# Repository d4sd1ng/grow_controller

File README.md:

# Growroom Control System

**Firmware (aktuelle Struktur):** [Sensor, Remote und C3](firmware/README.md). Die früheren Sketch-Ordner wurden entfernt; kein altes Installationsskript verwenden.

Streamlit dashboard for simulated sensors, VPD helpers, optional Telegram alerts, and GPIO simulation (runs anywhere with Python 3.11+).

**Aktuelle Sensor-Pinbelegung:** [Sensor/PINOUT.md](firmware/Sensor/PINOUT.md) · **Firmware:** [Sensor, Remote und C3](firmware/README.md) · **Deployment:** [deployment_vps.md](deployment_vps.md). Frühere Verdrahtungstexte sind nicht mehr gültig.

## Setup

```bash
python -m venv .venv
.venv\Scripts\activate   # Windows
pip install -r requirements.txt
```

Copy `.env.example` to `.env`. **Alle sensiblen und serverseitigen Settings** (Telegram, **`TELEMETRY_API_KEY`**, Ports, DB-Pfad, **`IOT_*`** für WLAN/Server-Host) kommen **nur aus `.env`** — der Python-Code nutzt `env_config`-Getter. Firmware: **`python export_firmware_secrets_from_env.py`** erzeugt git-ignorierte **`device_secrets.h`** pro Sketch aus derselben `.env`. **Telegram-Versand ist im Code aktuell auskommentiert** — Alerts landen in `alerts_log` und auf dem **CYD** (`/api/v1/mobile/summary`). Zum Reaktivieren in `main.py` die `telegram_notify`-Zeilen wieder einsetzen.

## Run

```bash
streamlit run main.py
```

**Telemetry-API** (ESP32 im Growroom → Server; **Cheap Yellow Display** holt die letzten Werte):

```bash
python run_telemetry_api.py
```

Standard: `http://<PC-IP>:8765` — u. a. `GET /api/v1/health` (SQLite-Ping, **ohne** API-Key), `POST /api/v1/telemetry`, `GET /api/v1/telemetry/series` (**echte Historie** aus SQLite, Parameter `hours` / `minutes` / `max_points`), `GET /api/v1/mobile/summary` (CYD: Messwerte + Relais + **Alerts**), `GET/POST /api/v1/control/*`. Optional **`X-Telemetry-Key`**. **`firmware/`**: Die aktuelle LVGL-Remote verwendet `/api/v1/mobile/summary` für Messwerte und `/api/v1/actuator/state` für den C3-Status.

Optional Telegram command bot (separate process; uses the same `.env` token):

```bash
python telegram_bot.py
```

## Telemetry (Speicher)

- Das Streamlit-Dashboard schreibt in **SQLite** nur, wenn sich Messwerte/Relais **merklich** ändern **oder** ein **Heartbeat** von ca. 60 s vergangen ist (weniger Reroll-Spam). ESP-/API-Ingest bleibt unverändert: jeder `POST /api/v1/telemetry` wie bisher eine Zeile.
- Speicherort: **`data/grow_telemetry.db`** standardmäßig (Ordner wird angelegt).
- Feste Spalten: Temperaturen, Luftfeuchte, Licht, EC, pH, vier Relais-Flags — passend zur Anzeige/Charts.
- Zusatzfelder aus dem ESP (andere Keys, verschachtelte Objekte) liegen als JSON in **`extras_json`** und gehen beim späteren Hardware-Import nicht verloren.
- **Retention:** alte Zeilen werden nach **`GROW_DATA_RETENTION_DAYS`** (Standard 90) gelöscht. **`GROW_DATA_DB=:memory:`** nur für Tests/ephemer.

Ursprünglich gedacht als zwei ESP32 (Sensoren + Relais) — **ein** Board reicht: Sensoren lesen, Relais schalten, ein Kanal (HTTP/MQTT/Serial) liefert JSON; der PC übernimmt Aggregation, Alerts und SQLite. Beim Anbinden echtes Payload-Felder auf die Tabellenspalten mappen (Relais ggf. aus `relays.heater` → Spalte `heater`).

## Security

**Eingrenzung:** Das Setup ist für ein **vertrauenswürdiges Heim-LAN** gedacht — nicht als hart abgesicherte Internet-API.

| Bereich | Stand im Projekt |
|--------|------------------|
| **Geheimnisse** | Tokens, API-Key, WLAN-Passwort nur in **`.env`** bzw. generiertem **`device_secrets.h`** (nicht committen). |
| **API-Zugriff** | Optional **`TELEMETRY_API_KEY`**: alle geschützten Routen verlangen Header **`X-Telemetry-Key`**. **Ohne** gesetzten Key ist die API im LAN für jeden erreichbar, der den Port nutzen kann. **`/api/v1/health`** bleibt **ohne** Key (nur DB-Erreichbarkeit, keine Messwerte). |
| **Transport** | **Python-Server:** typisch HTTP intern (Uvicorn); nach außen am VPS **HTTPS** (Proxy). **Firmware:** optional **`IOT_USE_HTTPS=1`** → TLS mit `WiFiClientSecure`; **`IOT_TLS_INSECURE=1`** überspringt Zertifikatscheck (MITM-Risiko). Heim-LAN ohne TLS: weiter **HTTP** möglich. |
| **Auswirkung** | **`POST /api/v1/control/*`** kann **Relais** und damit Heizung/Lüftung/Pumpe steuern — mit API-Key und Netztrennung absichern. |
| **Daten** | SQLite unter **`data/`** — Zugriff nur für den Server-Benutzer; Backups nicht öffentlich ablegen. |
| **CORS** | Standard **`TELEMETRY_CORS_ORIGINS=*`**; für Web-UI aus einer festen Origin ggf. einschränken. |
| **Telegram** | Bot-Token jemals in Git gelandet? In [BotFather](https://t.me/BotFather) **widerrufen** und neuen Token in `.env` setzen. |

**Pragmatische Maßnahmen:** `TELEMETRY_API_KEY` **setzen** (langer Zufallsstring), Telemetry-Port **nicht** ins Internet öffnen, Grow-Geräte in **Gast-WLAN / IoT-VLAN** mit Regeln nur zum Server-Port, Server und `.env` nur für vertrauenswürdige Konten.

## Tests

```bash
python -m unittest system_tests
```

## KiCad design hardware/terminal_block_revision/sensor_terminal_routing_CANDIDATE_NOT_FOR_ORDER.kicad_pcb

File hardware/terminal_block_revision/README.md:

# Schraubklemmen-Revision – beide Leiterplatten (28.11.2026)

Status: verbindliche mechanische Zielvorgabe des Nutzers; **Layout, Routing und Fertigungsprüfung stehen noch aus.** Nicht zur Fertigung.

| Platine | 12-polig | 2-polig | Kapazität | Bisherige Kontakte |
|---|---:|---:|---:|---:|
| Sensor Rev A | 3 | 1 | 38 | 38 |
| C3 R1 | 2 | 1 | 26 | 25 |
| Gesamt | 5 | 2 | 64 | 63 |

Die vorhandenen 24 steckbaren MSTBA-Grundleisten und 24 Gegenstecker sollen vollständig entfallen. Fest verlötete THT-Schraubklemmen, einreihig, horizontale Kabeleinführung, Raster 5,08 mm. Keine Änderung der bestehenden Anschlussfunktionen. Ein freier Kontakt auf der C3-Platine ist als Reserve zu kennzeichnen.

## Beschaffungskandidat (noch keine Bauteilfreigabe)
Same Sky TB004-508-12BE und TB004-508-02BE. Herstellerzeichnung: https://www.sameskydevices.com/product/resource/tb004-508.pdf (S. 2). Gehäusenennmaße 60,96 bzw. 10,16 x 10,20 mm, Höhe 14,10 mm; Lochreihe Ø1,60 mm, Raster 5,08 mm, Abstand erster/letzter Kontakt 55,88 bzw. 5,08 mm. Seitliche Verbindungsnase zusätzlich berücksichtigen.

Vorhandene CAD-/CAM-Dateien bleiben als historische Revision unverändert; sie enthalten noch die alte Phoenix-Variante. Keine neue Gerber-Freigabe ohne neue CAD-Prüfung. Die THT-Überarbeitung der übrigen C3-Bauteile bleibt eine getrennte Aufgabe. Keine Änderungen an Firmware oder elektrischer Funktion.

Die Bibliothek `TerminalBlock_Candidate.pretty` enthält eigenständig gezeichnete, ungeprüfte mechanische Footprint-Kandidaten für diese beiden Polzahlen. Pad-Außendurchmesser und Courtyard sind vorläufige CAD-Parameter und keine Herstellerfreigabe. Vor Verwendung mit Original-Footprint und Muster abgleichen.

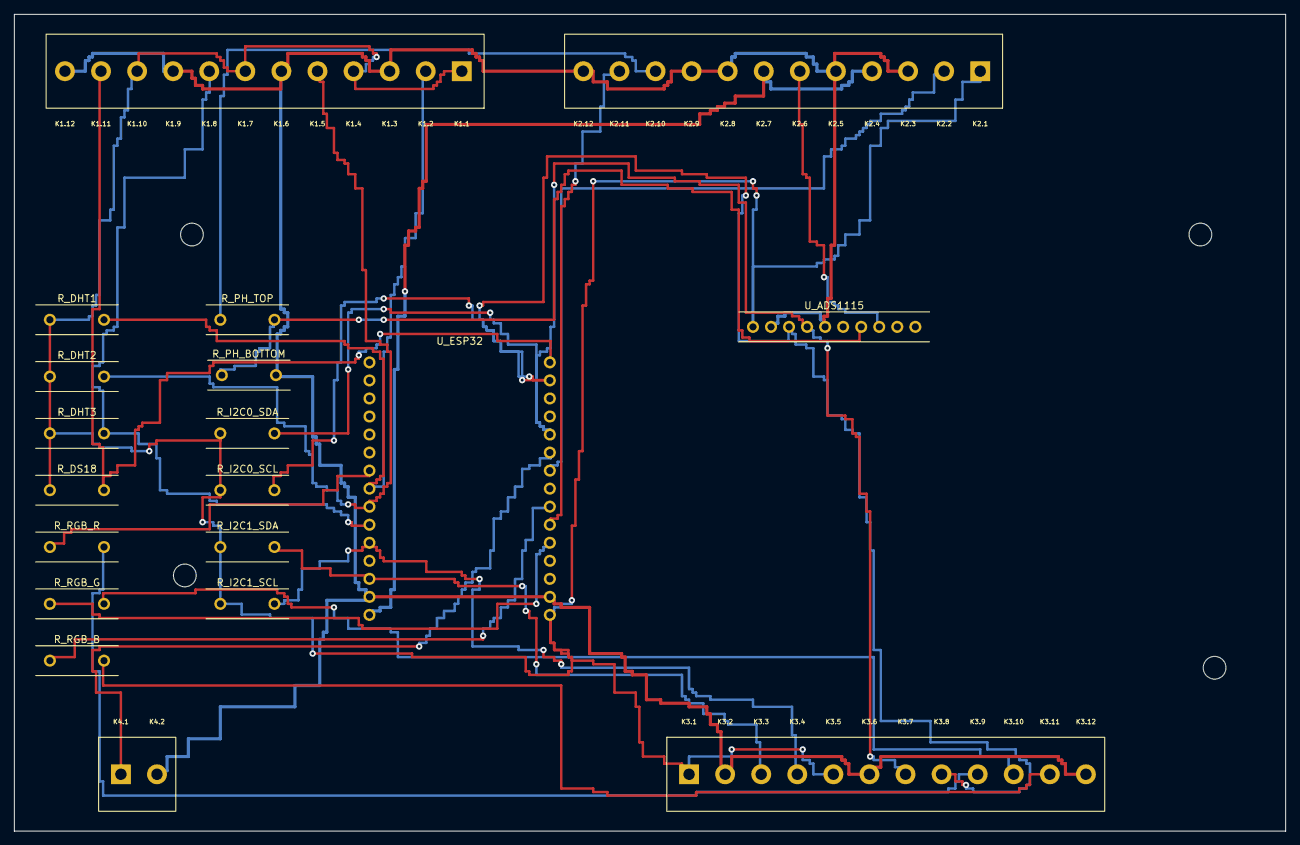
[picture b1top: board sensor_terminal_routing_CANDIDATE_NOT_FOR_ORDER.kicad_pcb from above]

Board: 2 copper layers, 179.0 x 115.0 mm, 23 parts (0 on the bottom side), 23 nets.

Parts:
H1, H2, H3, H4: MountingHole_3.2mm_M3; MountingHole_3p2_M3
K1, K2, K3: SameSky_TB004-508-12BE_CANDIDATE
K4: SameSky_TB004-508-02BE_CANDIDATE
R_DHT1, R_DHT2, R_DHT3: Resistor_Axial_P7.62; Axial_THT_DIN0207_P7p62
R_DS18: Resistor_Axial_P7.62; Axial_THT_DIN0207_P7p62
R_I2C0_SCL, R_I2C0_SDA, R_I2C1_SCL, R_I2C1_SDA: Resistor_Axial_P7.62; Axial_THT_DIN0207_P7p62
R_PH_BOTTOM: 20k; Axial_THT_DIN0207_P7p62
R_PH_TOP: 10k; Axial_THT_DIN0207_P7p62
R_RGB_B: Resistor_Axial_P7.62; Axial_THT_DIN0207_P7p62
R_RGB_G: Resistor_Axial_P7.62; Axial_THT_DIN0207_P7p62
R_RGB_R: Resistor_Axial_P7.62; Axial_THT_DIN0207_P7p62
U_ADS1115: ADS1115_10Pin_P2.54; ADS1115_Module_1x10_P2p54
U_ESP32: ESP32_30Pin_28x51mm; ESP32_30Pin_25p40_28x51

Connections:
3V3: K1.1, K1.4, K1.7, K1.10, K2.1, K3.1, K3.5, R_DHT1.1, R_DHT2.1, R_DHT3.1, R_DS18.1, R_I2C0_SCL.1, R_I2C0_SDA.1, R_I2C1_SCL.1, R_I2C1_SDA.1, U_ADS1115.1, U_ESP32.16
5V_USB_BOARD: K2.4, K2.7, U_ESP32.15
DHT1_DATA: K1.2, R_DHT1.2, U_ESP32.8
DHT2_DATA: K1.5, R_DHT2.2, U_ESP32.9
DHT3_DATA: K1.8, R_DHT3.2, U_ESP32.10
DS18_DATA: K1.11, R_DS18.2, U_ESP32.30
EC_ANALOG_UNVERIFIED: K2.6, U_ADS1115.8
GND: K1.3, K1.6, K1.9, K1.12, K2.3, K2.5, K2.8, K2.9, K2.12, K3.2, K3.6, K3.12, K4.2, R_PH_BOTTOM.2, U_ADS1115.2, U_ADS1115.5, U_ESP32.14, U_ESP32.17
I2C_BH_SCL: K3.4, R_I2C1_SCL.2, U_ESP32.11
I2C_BH_SDA: K3.3, R_I2C1_SDA.2, U_ESP32.13
I2C_MAIN_SCL: K3.8, R_I2C0_SCL.2, U_ADS1115.3, U_ESP32.29
I2C_MAIN_SDA: K3.7, R_I2C0_SDA.2, U_ADS1115.4, U_ESP32.26
LEVEL_TX: K2.2, U_ESP32.24
PHASE_BUTTON: K2.11, U_ESP32.21
PH_A0_CONDITIONED_UNVERIFIED: R_PH_BOTTOM.1, R_PH_TOP.2, U_ADS1115.7
PH_PO_UNVERIFIED: K2.10, R_PH_TOP.1
RGB_B_GPIO: R_RGB_B.1, U_ESP32.22
RGB_B_LED: K3.11, R_RGB_B.2
RGB_G_GPIO: R_RGB_G.1, U_ESP32.20
RGB_G_LED: K3.10, R_RGB_G.2
RGB_R_GPIO: R_RGB_R.1, U_ESP32.7
RGB_R_LED: K3.9, R_RGB_R.2
SERVICE_BUTTON: K4.1, U_ESP32.25

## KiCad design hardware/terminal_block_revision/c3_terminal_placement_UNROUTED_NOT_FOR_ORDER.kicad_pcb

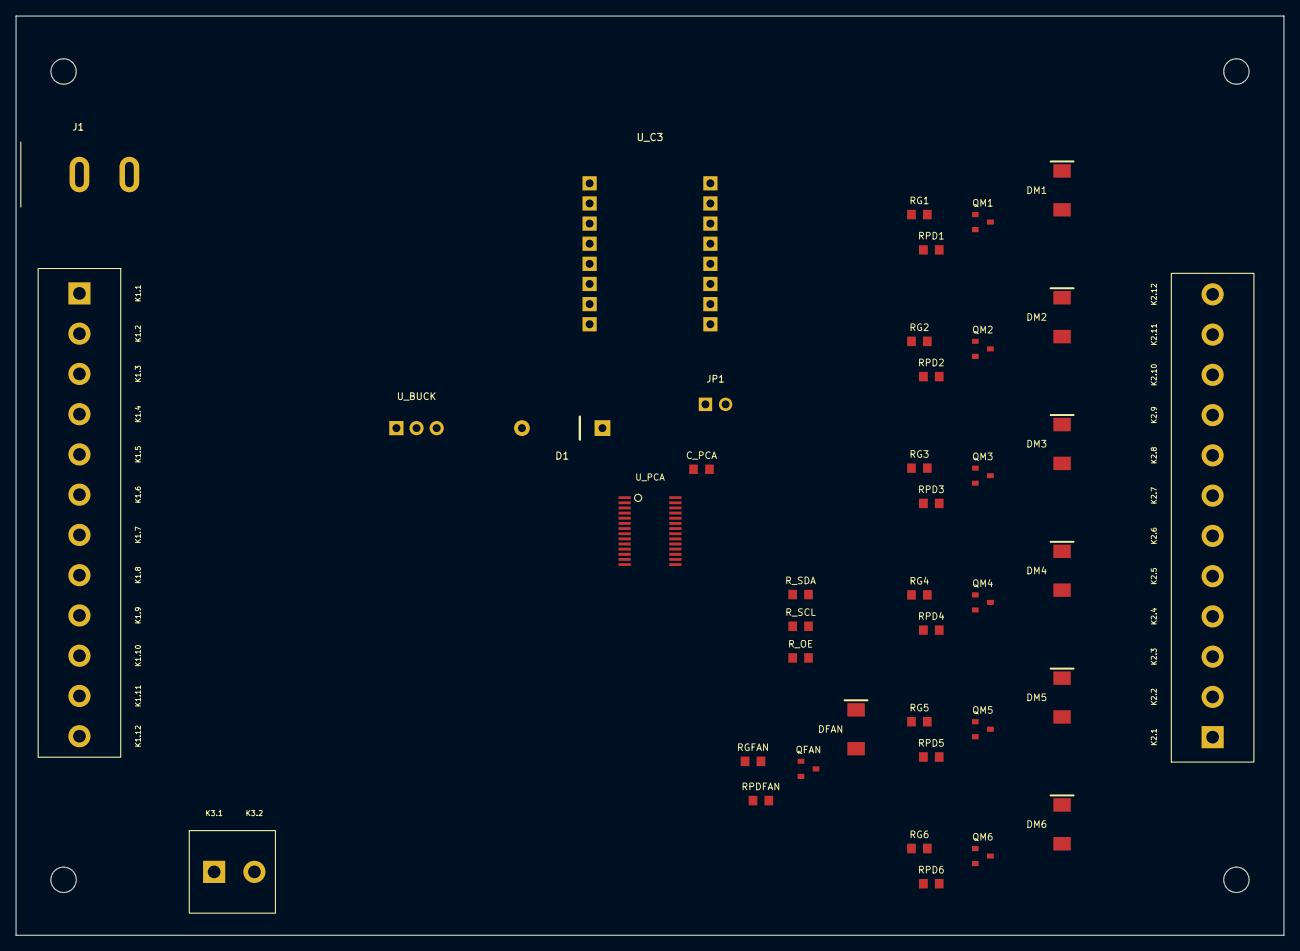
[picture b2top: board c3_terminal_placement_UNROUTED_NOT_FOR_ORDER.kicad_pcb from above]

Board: 2 copper layers, 160.0 x 116.0 mm, 45 parts (0 on the bottom side), 35 nets, no tracks yet.

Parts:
C_PCA: 100n; R_0805_HandSolder_2p0
D1: 1N5819; D_DO41_P10p16_CathodeRight
DFAN: SS34; SS34_SMA_K_North
DM1, DM2, DM3, DM4, DM5, DM6: SS34; SS34_SMA_K_North
H1, H2, H3, H4: M3; MountingHole_3p2_M3
J1: PJ-037AH; SameSky_PJ-037AH_THT_LeftFacing
JP1: SERVICE_POWER_LINK; PowerLink_1x02_P2p54
K1, K2: SameSky_TB004-508-12BE_CANDIDATE
K3: SameSky_TB004-508-02BE_CANDIDATE
QFAN: AO3400A; AO3400A_SOT23_GSD
QM1, QM2, QM3, QM4, QM5, QM6: AO3400A; AO3400A_SOT23_GSD
RG1, RG2, RG3, RG4, RG5, RG6: 100R; R_0805_HandSolder_2p0
RGFAN: 100R; R_0805_HandSolder_2p0
RPD1, RPD2, RPD3, RPD4, RPD5, RPD6: 100k; R_0805_HandSolder_2p0
RPDFAN: 100k; R_0805_HandSolder_2p0
R_OE: 10k; R_0805_HandSolder_2p0
R_SCL: 4k7; R_0805_HandSolder_2p0
R_SDA: 4k7; R_0805_HandSolder_2p0
U_BUCK: R-78E5.0-1.0; RECOM_R-78E5.0-1.0_SIP3
U_C3: ESP32-C3 SUPERMINI; ESP32_C3_SuperMini_2x8_15p24
U_PCA: PCA9685PW; PCA9685PW_TSSOP28_4p4x9p7

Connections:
3V3_LOGIC: C_PCA.1, R_OE.1, R_SCL.1, R_SDA.1, U_C3.3, U_PCA.28
+5V_BUCK: D1.2, U_BUCK.3
+5V_DIODE: D1.1, JP1.1
+5V_PROTECTED: JP1.2, U_C3.1
+12V_IN: DFAN.1, DM1.1, DM2.1, DM3.1, DM4.1, DM5.1, DM6.1, J1.1, K1.10, K2.1, K2.3, K2.5, K2.7, K2.9, K2.11, U_BUCK.1
CTRL1_GPIO: K1.2, U_C3.8
CTRL2_GPIO: K1.4, U_C3.7
CTRL3_GPIO: K1.6, U_C3.5
CTRL4_GPIO: K1.8, U_C3.4
CTRL5_GPIO: K3.2, U_C3.9
FAN_CTRL: RGFAN.1, U_PCA.12
FAN_GATE: QFAN.1, RGFAN.2, RPDFAN.2
FAN_SW: DFAN.2, K1.9, QFAN.3
GND: C_PCA.2, J1.2, K1.1, K1.3, K1.5, K1.7, K3.1, QFAN.2, QM1.2, QM2.2, QM3.2, QM4.2, QM5.2, QM6.2, RPD1.1, RPD2.1, RPD3.1, RPD4.1, RPD5.1, RPD6.1, RPDFAN.1, U_BUCK.2, U_C3.2, U_PCA.1, U_PCA.2, U_PCA.3, U_PCA.4, U_PCA.5, U_PCA.14, U_PCA.24, U_PCA.25
I2C_SCL_GPIO10: R_SCL.2, U_C3.14, U_PCA.26
I2C_SDA_GPIO7: R_SDA.2, U_C3.11, U_PCA.27
M1_CTRL: RG1.1, U_PCA.6
M1_GATE: QM1.1, RG1.2, RPD1.2
M1_SW: DM1.2, K2.2, QM1.3
M2_CTRL: RG2.1, U_PCA.7
M2_GATE: QM2.1, RG2.2, RPD2.2
M2_SW: DM2.2, K2.4, QM2.3
M3_CTRL: RG3.1, U_PCA.8
M3_GATE: QM3.1, RG3.2, RPD3.2
M3_SW: DM3.2, K2.6, QM3.3
M4_CTRL: RG4.1, U_PCA.9
M4_GATE: QM4.1, RG4.2, RPD4.2
M4_SW: DM4.2, K2.8, QM4.3
M5_CTRL: RG5.1, U_PCA.10
M5_GATE: QM5.1, RG5.2, RPD5.2
M5_SW: DM5.2, K2.10, QM5.3
M6_CTRL: RG6.1, U_PCA.11
M6_GATE: QM6.1, RG6.2, RPD6.2
M6_SW: DM6.2, K2.12, QM6.3
PCA_OE_GPIO20: R_OE.2, U_C3.15, U_PCA.23

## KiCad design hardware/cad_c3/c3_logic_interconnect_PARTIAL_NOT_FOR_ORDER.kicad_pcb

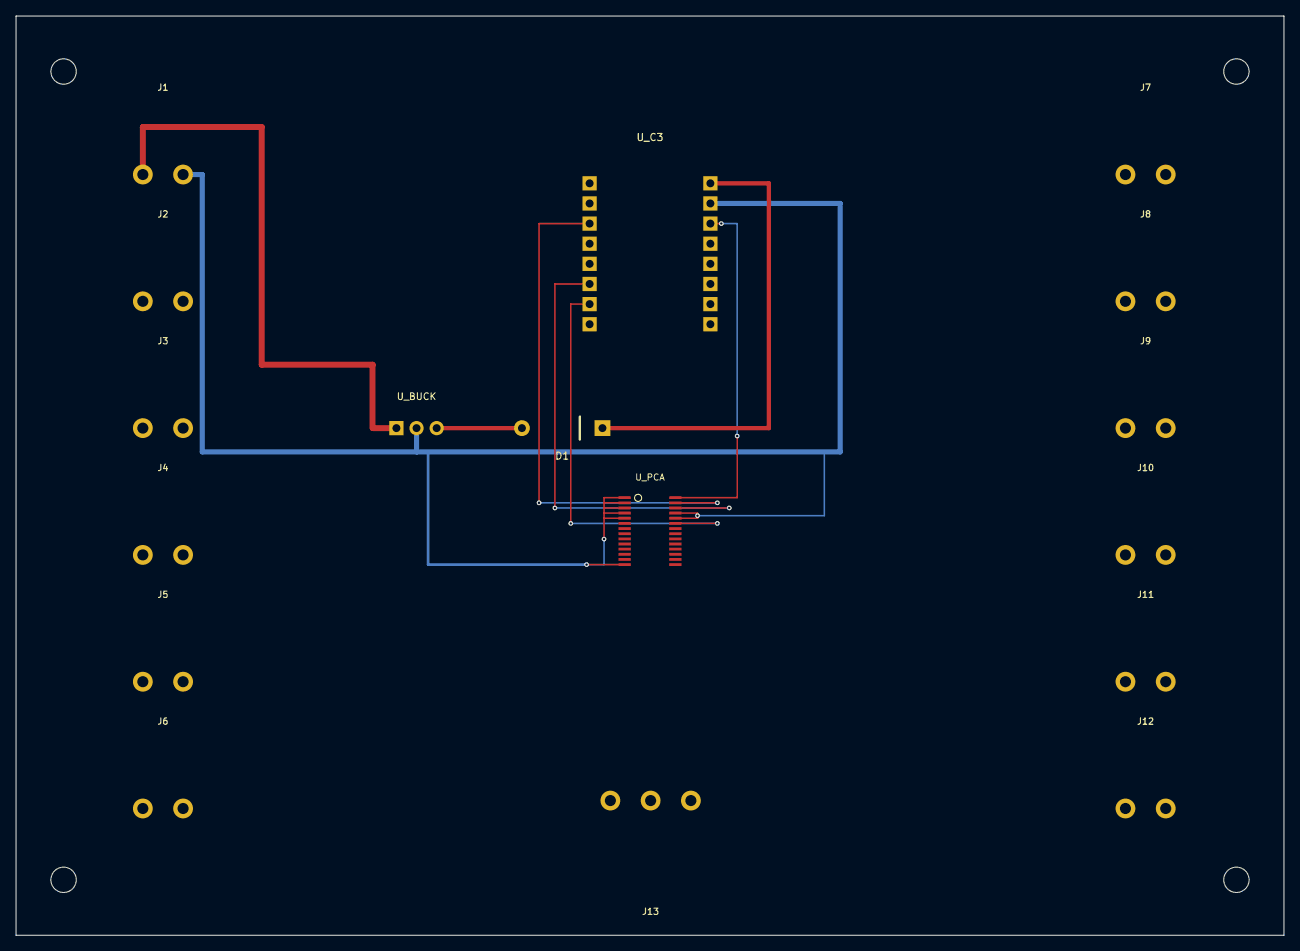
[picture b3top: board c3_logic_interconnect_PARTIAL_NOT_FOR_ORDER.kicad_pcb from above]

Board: 2 copper layers, 160.0 x 116.0 mm, 21 parts (0 on the bottom side), 8 nets.

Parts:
D1: 1N5819; D_DO41_P10p16_CathodeRight
H1, H2, H3, H4: M3; MountingHole_3p2_M3
J1, J2, J3, J4, J5, J6, J7, J8, J9, J10, J11, J12: PHOENIX_1757242; MSTBA_2P_5p08_NORTH
J13: PHOENIX_1757255; MSTBA_3P_5p08_SOUTH
U_BUCK: R-78E5.0-1.0; RECOM_R-78E5.0-1.0_SIP3
U_C3: ESP32-C3 SUPERMINI; ESP32_C3_SuperMini_2x8_15p24
U_PCA: PCA9685PW; PCA9685PW_TSSOP28_4p4x9p7

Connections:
3V3_LOGIC: U_C3.3, U_PCA.28
+5V_BUCK: D1.2, U_BUCK.3
+5V_PROTECTED: D1.1, U_C3.1
+12V_IN: J1.1, U_BUCK.1
GND: J1.2, U_BUCK.2, U_C3.2, U_PCA.1, U_PCA.2, U_PCA.3, U_PCA.4, U_PCA.5, U_PCA.14, U_PCA.24, U_PCA.25
I2C_SCL_GPIO10: U_C3.14, U_PCA.26
I2C_SDA_GPIO7: U_C3.11, U_PCA.27
PCA_OE_GPIO20: U_C3.15, U_PCA.23
